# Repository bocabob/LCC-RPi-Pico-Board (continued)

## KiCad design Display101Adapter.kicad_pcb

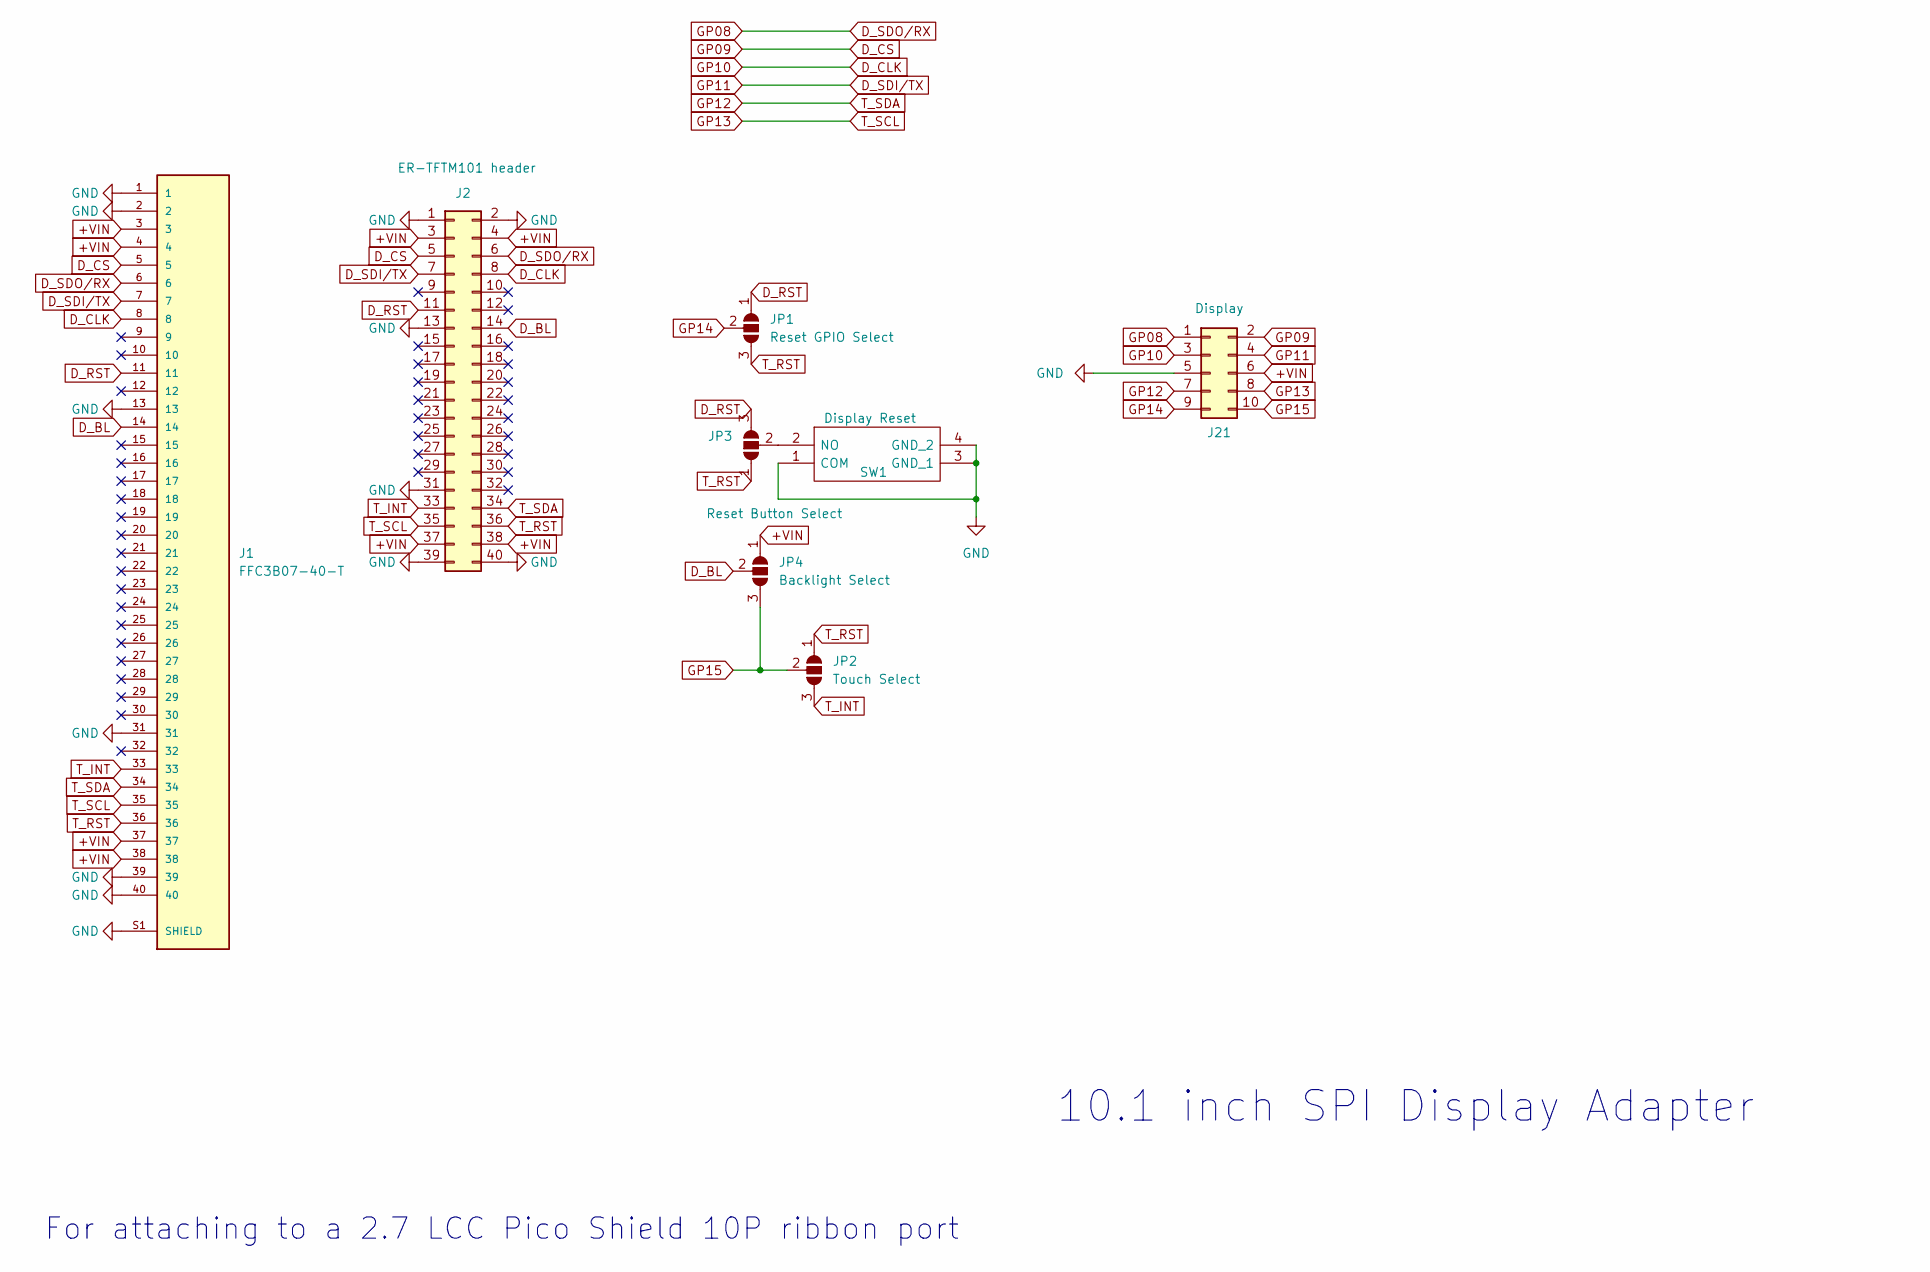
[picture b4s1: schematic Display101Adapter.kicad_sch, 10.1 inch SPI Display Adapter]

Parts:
J1: FFC3B07-40-T; GCT_FFC3B07-40-T; PARTREV A
J2: ER-TFTM101 header; PinSocket_2x20_P2.54mm_Vertical
J21: Display; IDC-Header_2x05_P2.54mm_Vertical
JP1: Reset GPIO Select; SolderJumper-3_P1.3mm_Open_Pad1.0x1.5mm_NumberLabels
JP2: Touch Select; SolderJumper-3_P1.3mm_Open_Pad1.0x1.5mm_NumberLabels
JP3: Reset Button Select; SolderJumper-3_P1.3mm_Open_Pad1.0x1.5mm_NumberLabels
JP4: Backlight Select; SolderJumper-3_P1.3mm_Open_Pad1.0x1.5mm_NumberLabels
SW1: Display Reset; TS1167443BK160RAD; Mouser Part Number 179-TS1167443160RAD

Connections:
+VIN: J1.3, J1.4, J1.37, J1.38, J2.3, J2.4, J2.37, J2.38, J21.6, JP4.1 (A)
D_BL: J1.14, J2.14, JP4.2 (C)
D_CLK: J1.8, J2.8, J21.3
D_CS: J1.5, J2.5, J21.2
D_RST: J1.11, J2.11, JP1.1 (A), JP3.3 (B)
D_SDI/TX: J1.7, J2.7, J21.4
D_SDO/RX: J1.6, J2.6, J21.1
GND: J1.1, J1.2, J1.13, J1.31, J1.39, J1.40, J1.S1 (SHIELD), J1.S2 (SHIELD), J2.1, J2.2, J2.13, J2.31, J2.39, J2.40, J21.5, SW1.1 (COM), SW1.3 (GND_1), SW1.4 (GND_2)
GP12: J1.34, J2.34, J21.7
GP13: J1.35, J2.35, J21.8
GP14: J21.9, JP1.2 (C)
GP15: J21.10, JP2.2 (C), JP4.3 (B)
unnamed: JP3.2 (C), SW1.2 (NO)
T_INT: J1.33, J2.33, JP2.3 (B)
T_RST: J1.36, J2.36, JP1.3 (B), JP2.1 (A), JP3.1 (A)

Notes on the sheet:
10.1 inch SPI Display Adapter
For attaching to a 2.7 LCC Pico Shield 10P ribbon port

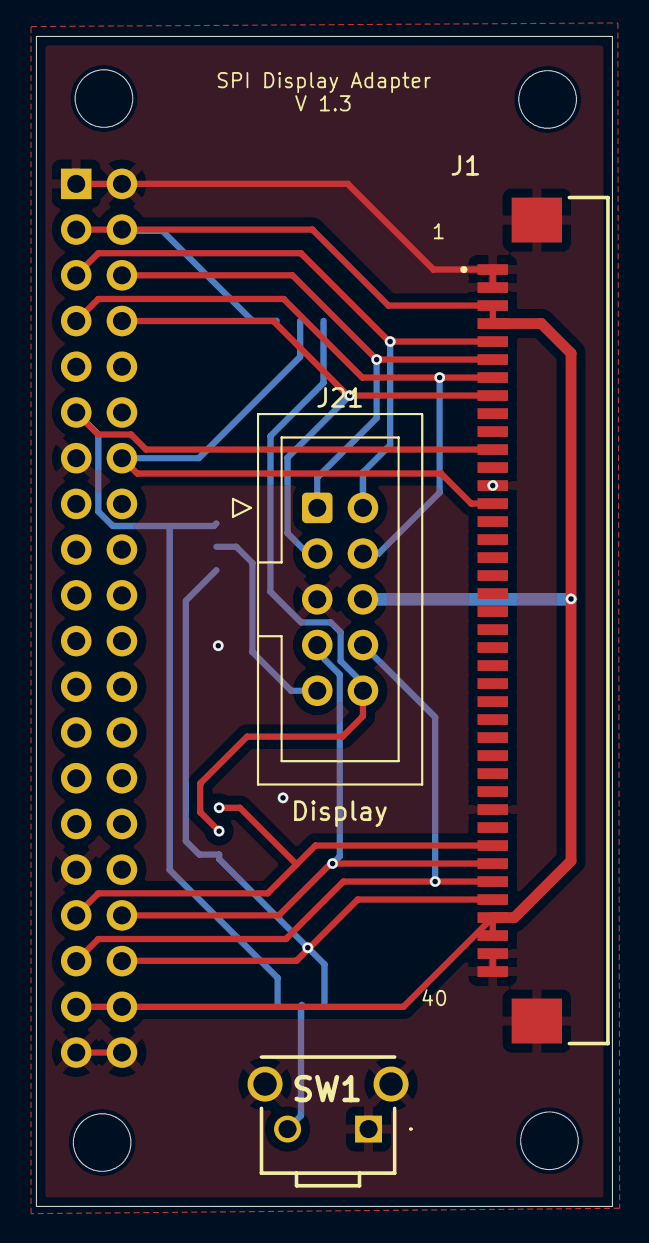
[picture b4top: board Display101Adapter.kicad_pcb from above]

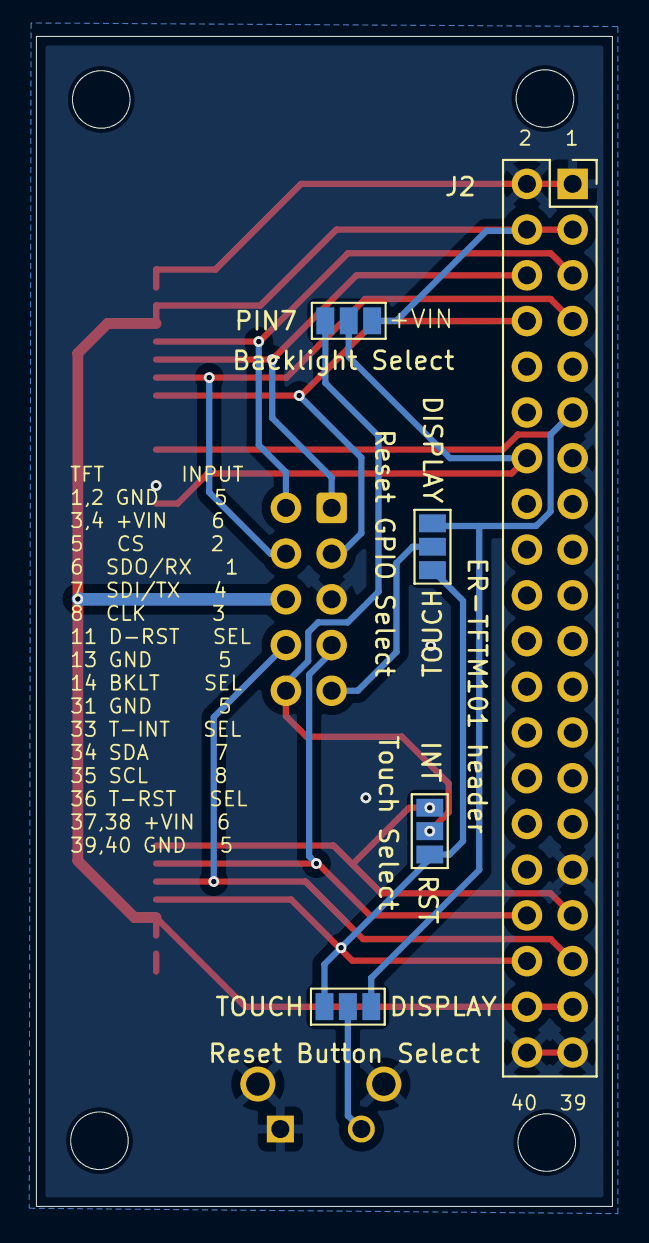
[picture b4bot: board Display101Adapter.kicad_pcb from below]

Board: 2 copper layers, 32.0 x 65.0 mm, 8 parts (5 on the bottom side), 15 nets.

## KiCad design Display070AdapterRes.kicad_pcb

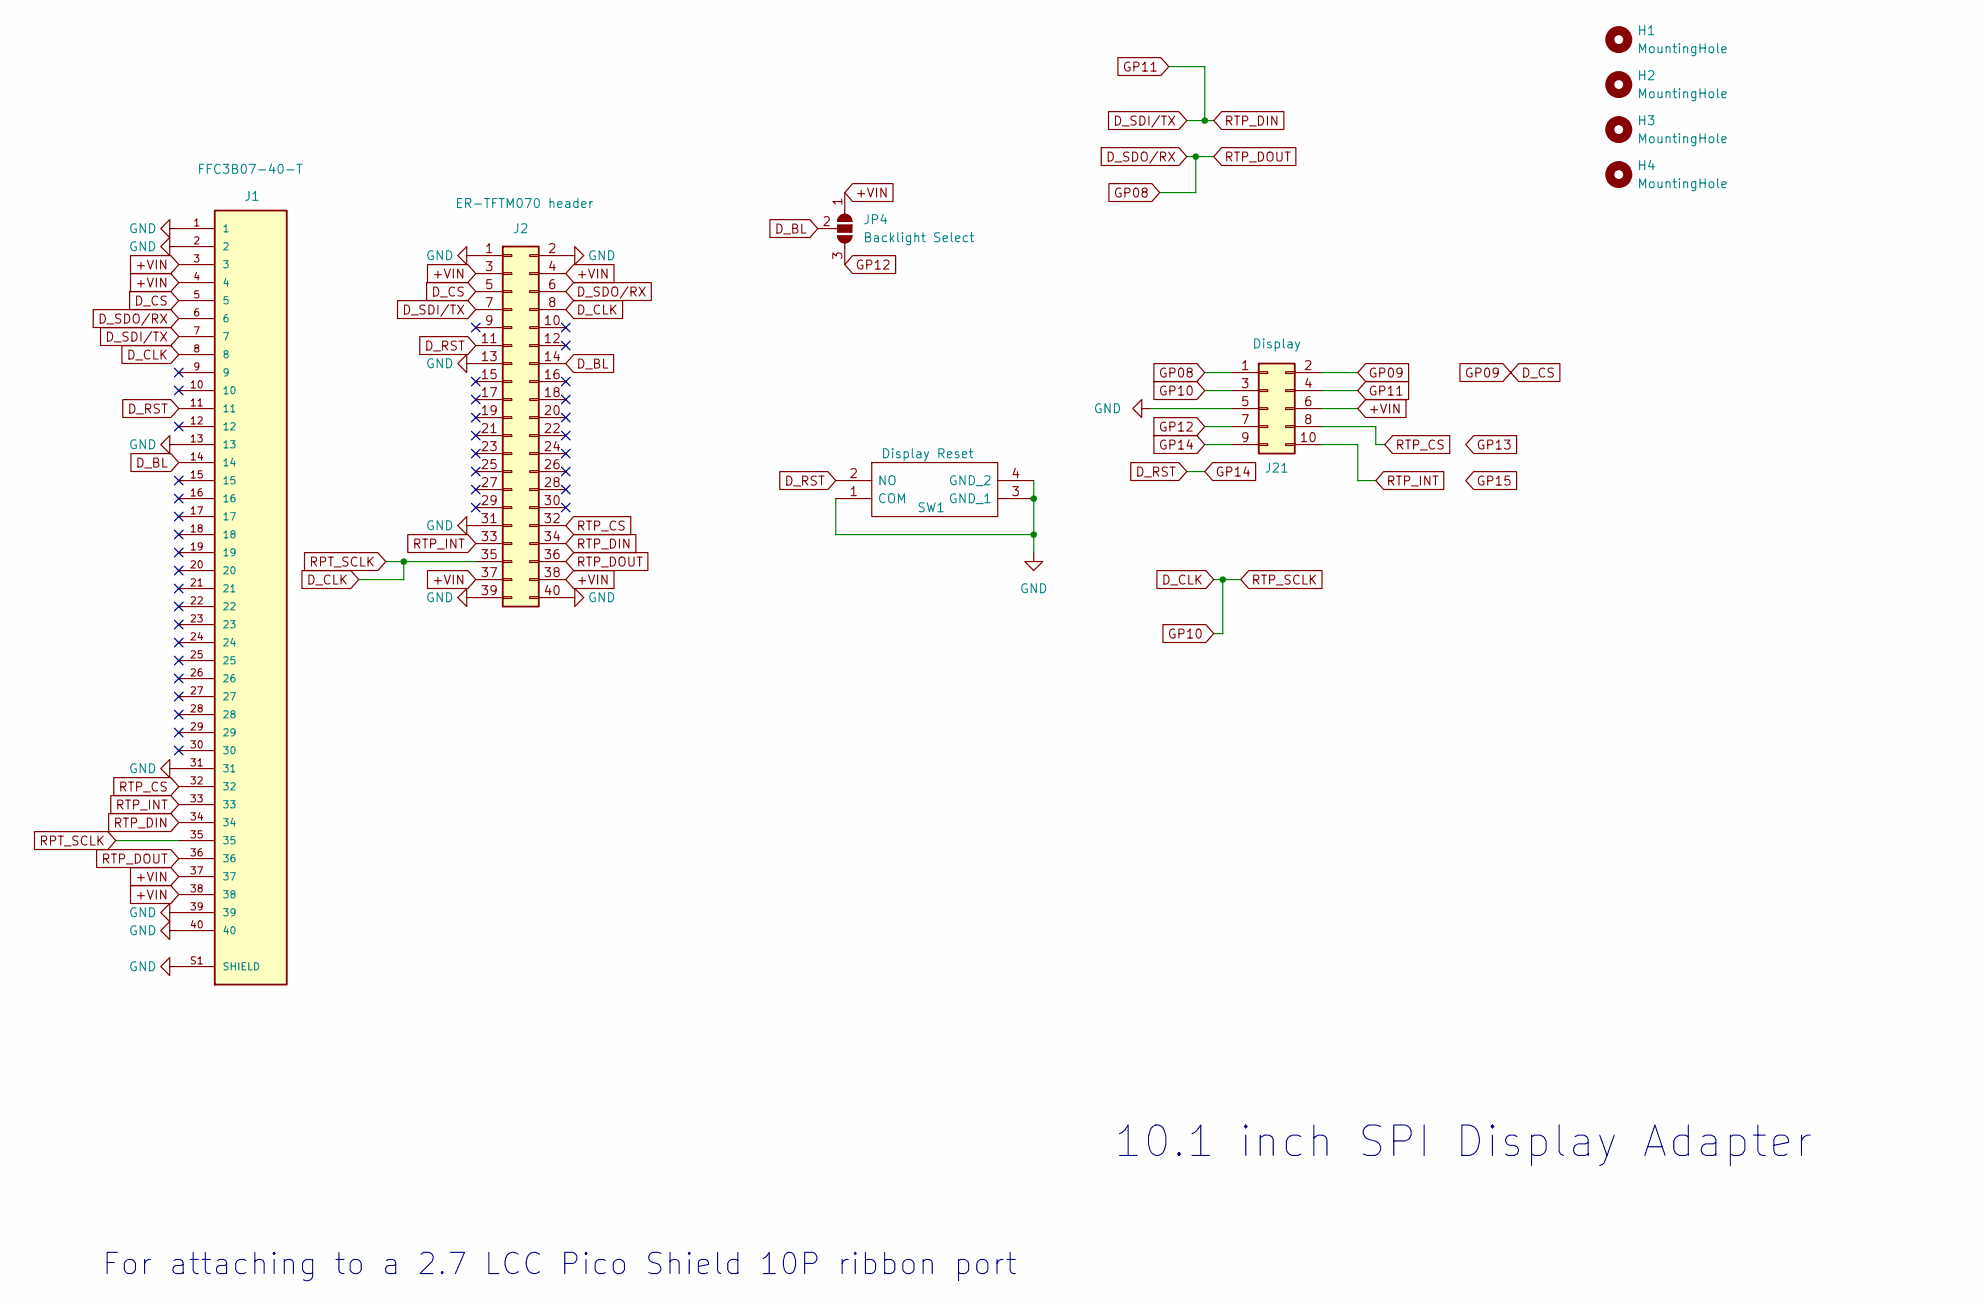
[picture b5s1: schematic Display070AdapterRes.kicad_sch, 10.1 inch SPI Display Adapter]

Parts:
H1, H2, H3, H4: MountingHole; MountingHole_3.5mm
J1: FFC3B07-40-T; GCT_FFC3B07-40-T; PARTREV A
J2: ER-TFTM070 header; PinSocket_2x20_P2.54mm_Vertical
J21: Display; IDC-Header_2x05_P2.54mm_Vertical
JP4: Backlight Select; SolderJumper-3_P1.3mm_Open_Pad1.0x1.5mm_NumberLabels
SW1: Display Reset; TS1167443BK160RAD; Mouser Part Number 179-TS1167443160RAD

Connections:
+VIN: J1.3, J1.4, J1.37, J1.38, J2.3, J2.4, J2.37, J2.38, J21.6, JP4.1 (A)
D_BL: J1.14, J2.14, JP4.2 (C)
D_CLK: J1.8, J1.35, J2.8, J2.35, J21.3
D_CS: J1.5, J2.5, J21.2
D_RST: J1.11, J2.11, J21.9, SW1.2 (NO)
D_SDI/TX: J1.7, J1.34, J2.7, J2.34, J21.4
D_SDO/RX: J1.6, J1.36, J2.6, J2.36, J21.1
GND: J1.1, J1.2, J1.13, J1.31, J1.39, J1.40, J1.S1 (SHIELD), J1.S2 (SHIELD), J2.1, J2.2, J2.13, J2.31, J2.39, J2.40, J21.5, SW1.1 (COM), SW1.3 (GND_1), SW1.4 (GND_2)
GP12: J21.7, JP4.3 (B)
RTP_CS: J1.32, J2.32, J21.8
RTP_INT: J1.33, J2.33, J21.10

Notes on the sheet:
10.1 inch SPI Display Adapter
For attaching to a 2.7 LCC Pico Shield 10P ribbon port

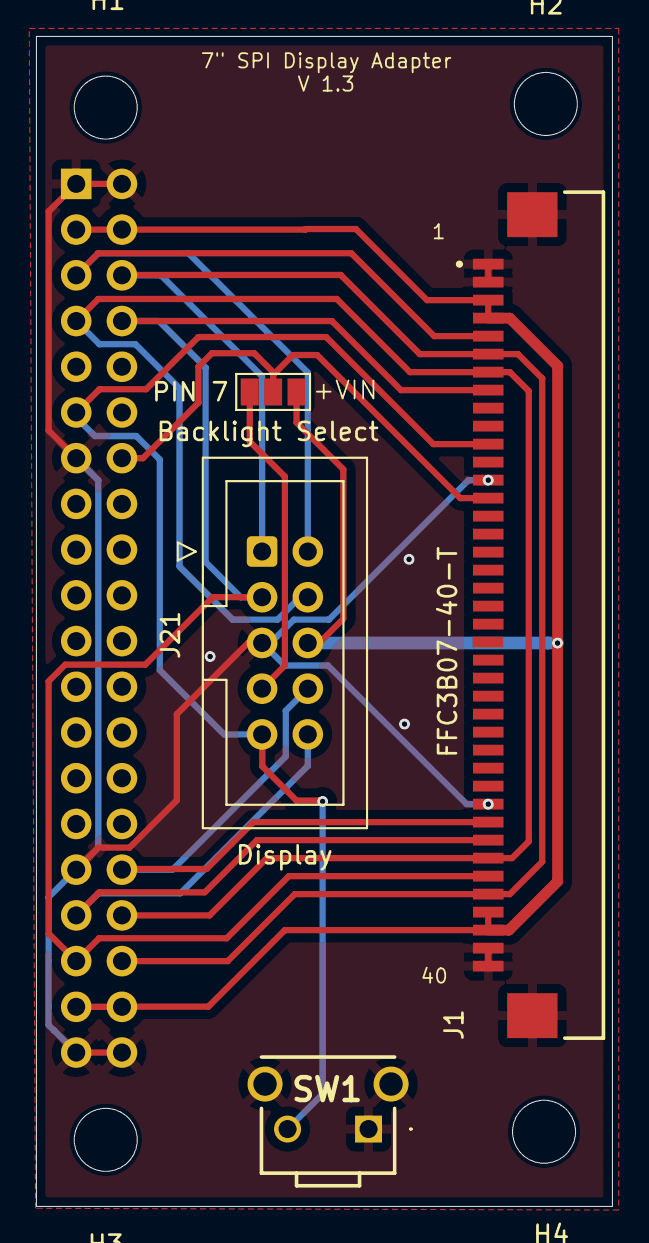
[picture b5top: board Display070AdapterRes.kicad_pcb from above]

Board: 2 copper layers, 32.0 x 65.0 mm, 9 parts (1 on the bottom side), 11 nets.

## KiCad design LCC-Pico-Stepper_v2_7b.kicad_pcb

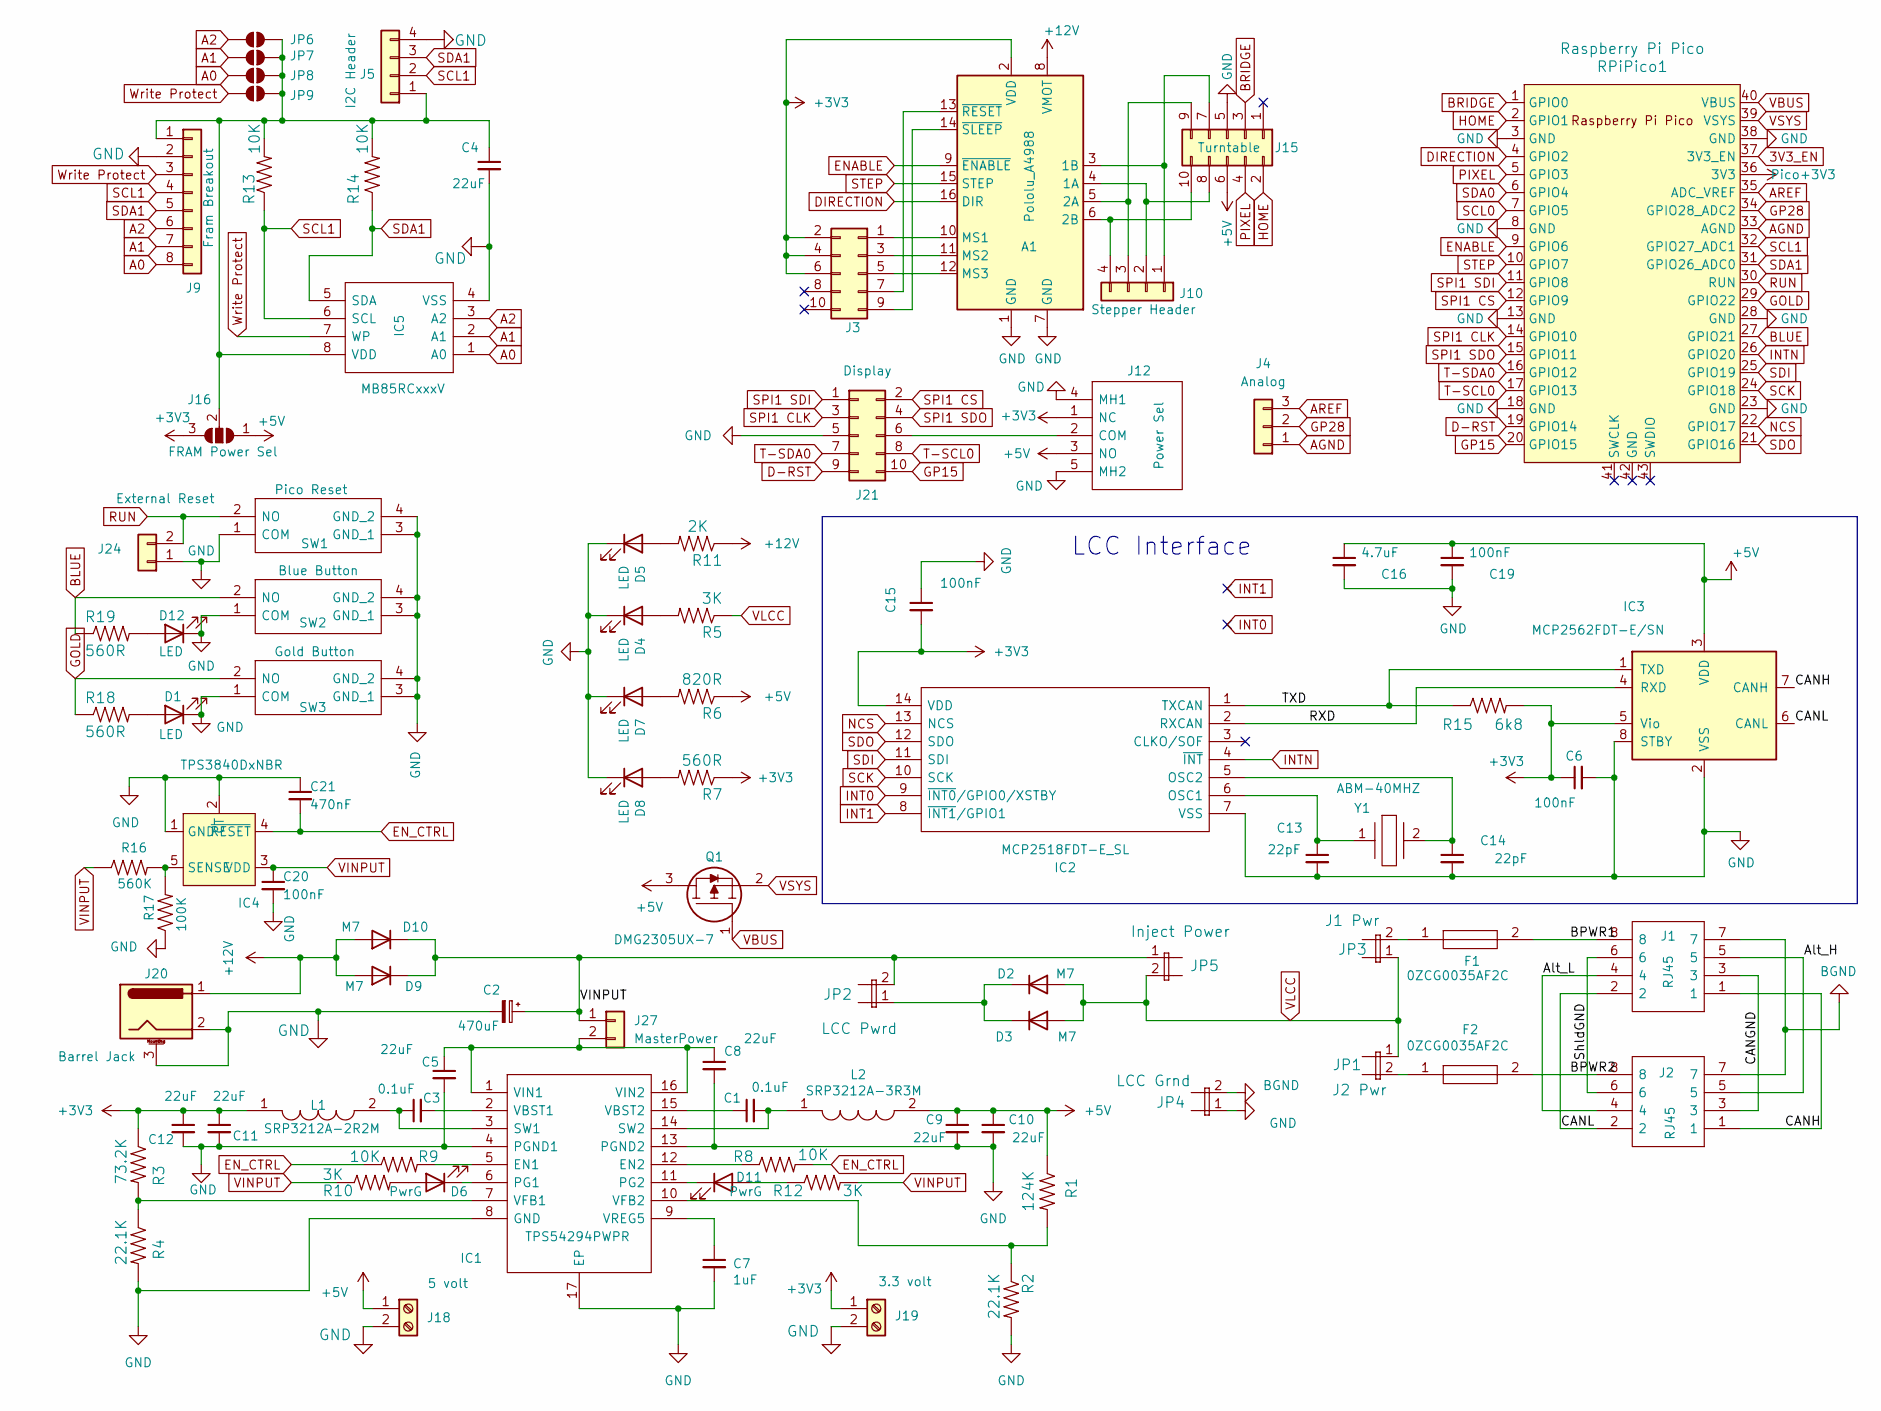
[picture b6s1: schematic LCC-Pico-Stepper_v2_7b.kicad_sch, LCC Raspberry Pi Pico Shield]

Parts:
A1: Pololu_A4988; Pololu_Breakout-16_15.2x20.3mm
C1, C3: 0.1uF; C_1206_3216Metric_Pad1.33x1.80mm_HandSolder
C2: 470uF; CP_Radial_D8.0mm_P3.50mm
C4, C5, C8, C9, C10, C11, C12: 22uF; C_1206_3216Metric_Pad1.33x1.80mm_HandSolder
C6, C15, C19, C20: 100nF; C_1206_3216Metric_Pad1.33x1.80mm_HandSolder
C7: 1uF; C_1206_3216Metric_Pad1.33x1.80mm_HandSolder
C13, C14: 22pF; C_1206_3216Metric_Pad1.33x1.80mm_HandSolder
C16: 4.7uF; C_1206_3216Metric_Pad1.33x1.80mm_HandSolder
C21: 470nF; C_1206_3216Metric_Pad1.33x1.80mm_HandSolder
D1, D4, D5, D7, D8, D12: LED; LED_1206_3216Metric_Pad1.42x1.75mm_HandSolder
D2, D3, D9, D10: M7; DIOM5327X240N
D6, D11: PwrG; LED_1206_3216Metric_Pad1.42x1.75mm_HandSolder
F1, F2: 0ZCG0035AF2C; FUSC4632X70N; Mouser Part Number 530-0ZCG0035AF2C
IC1: TPS54294PWPR; SOP65P640X120-17N; Mouser Part Number 595-TPS54294PWPR
IC2: MCP2518FDT-E_SL; SOIC-14_3.9x8.7mm_P1.27mm; Mouser Part Number 579-MCP2518FDT-E/SL
IC3: MCP2562FDT-E/SN; SOIC-8_3.9x4.9mm_P1.27mm; Mouser Part Number 771-TJA1042T/3/1J
IC4: TPS3840DxNBR; SOT-23-5
IC5: MB85RCxxxV; SOIC127P600X175-8N; Mouser Part Number 249-MB85RC256VPNJNE1
J1, J2: RJ45; MTJ880X1; Mouser Part Number 737-MTJ-880X1
J3: Conn_02x05_Odd_Even; PinHeader_2x05_P2.54mm_Vertical
J4: Analog
J5: I2C Header; PinSocket_1x04_P2.54mm_Vertical
J9: Fram Breakout; PinHeader_1x08_P2.54mm_Vertical
J10: Stepper Header; PinSocket_1x04_P2.54mm_Vertical
J12: Power Sel; SLW8645872ARAND; Mouser Part Number 179-SLW8645872ARAND
J15: Turntable; IDC-Header_2x05_P2.54mm_Vertical
J16: FRAM Power Sel; SolderJumper-3_P1.3mm_Open_RoundedPad1.0x1.5mm
J18: 5 volt; TerminalBlock_TE_282834-2_1x02_P2.54mm_Horizontal
J19: 3.3 volt; TerminalBlock_TE_282834-2_1x02_P2.54mm_Horizontal
J20: Barrel Jack; BarrelJack_Horizontal
J21: Display; IDC-Header_2x05_P2.54mm_Vertical
J24: External Reset; PinHeader_1x02_P2.54mm_Vertical
J27: MasterPower; PinHeader_1x02_P2.54mm_Vertical
JP1: J2 Pwr; PinHeader_1x02_P2.54mm_Vertical
JP2: LCC Pwrd; PinHeader_1x02_P2.54mm_Vertical
JP3: J1 Pwr; PinHeader_1x02_P2.54mm_Vertical
JP4: LCC Grnd; PinHeader_1x02_P2.54mm_Vertical
JP5: Inject Power; PinHeader_1x02_P2.54mm_Vertical
JP6: A2; SolderJumper-2_P1.3mm_Open_Pad1.0x1.5mm
JP7: A1; SolderJumper-2_P1.3mm_Open_Pad1.0x1.5mm
JP8: A0; SolderJumper-2_P1.3mm_Open_Pad1.0x1.5mm
JP9: WP; SolderJumper-2_P1.3mm_Open_Pad1.0x1.5mm
L1: SRP3212A-2R2M; INDC3225X120N; Mouser Part Number 652-SRP3212A-3R3M
L2: SRP3212A-3R3M; INDC3225X120N; Mouser Part Number 652-SRP3212A-3R3M
Q1: DMG2305UX-7; SOT96P240X115-3N; Mouser Part Number 621-DMG2305UX-7
R1: 124K; R_1206_3216Metric_Pad1.30x1.75mm_HandSolder
R2, R4: 22.1K; R_1206_3216Metric_Pad1.30x1.75mm_HandSolder
R3: 73.2K; R_1206_3216Metric_Pad1.30x1.75mm_HandSolder
R5, R10, R12: 3K; R_1206_3216Metric_Pad1.30x1.75mm_HandSolder
R6: 820R; R_1206_3216Metric_Pad1.30x1.75mm_HandSolder
R7, R18, R19: 560R; R_1206_3216Metric_Pad1.30x1.75mm_HandSolder
R8, R9, R13, R14: 10K; R_1206_3216Metric_Pad1.30x1.75mm_HandSolder
R11: 2K; R_1206_3216Metric_Pad1.30x1.75mm_HandSolder
R15: 6k8; R_1206_3216Metric_Pad1.30x1.75mm_HandSolder
R16: 560K; R_1206_3216Metric_Pad1.30x1.75mm_HandSolder
R17: 100K; R_1206_3216Metric_Pad1.30x1.75mm_HandSolder
RPiPico1: Raspberry Pi Pico; RPi_Pico_SMD_TH; PARTREV 12/May/2017
SW1: Pico Reset; TS1167443BK160RAD; Mouser Part Number 179-TS1167443160RAD
SW2: Blue Button; TS1167443BK160RAD; Mouser Part Number 179-TS1167443160RAD
SW3: Gold Button; TS1167443BK160RAD; Mouser Part Number 179-TS1167443160RAD
Y1: ABM-40MHZ; ABM3; Mouser Part Number 815-ABL-40-B2F

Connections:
3V3_EN: RPiPico1.37 (3V3_EN)
+3V3: A1.2 (VDD), C6.1, C11.1, C12.1, C15.2, IC2.14 (VDD), IC3.5 (Vio), J3.2, J3.4, J3.6, J12.1 (NC), J16.3 (B), J19.1, L1.1, R3.1, R7.1, R15.2
+5V: C9.1, C10.1, C16.1, C19.1, IC3.3 (VDD), J12.3 (NO), J15.6, J16.1 (A), J18.1, L2.2, Q1.3, R1.1, R6.1
+12V: A1.8 (VMOT), D9.2 (A), D10.2 (A), J20.1, R11.1
/Alt_H: J1.5, J2.5
/Alt_L: J1.4, J2.4
/BPWR1: F1.2, J1.8
/BPWR2: F2.2, J2.8
/CANGND: J1.3, J2.3
/CANH: IC3.7 (CANH), J1.1, J2.1
/CANL: IC3.6 (CANL), J1.2, J2.2
/RXD: IC2.2 (RXCAN), IC3.4 (RXD)
/ShldGND: J1.6, J2.6
/TXD: IC2.1 (TXCAN), IC3.1 (TXD), R15.1
A0: IC5.1 (A0), J9.8, JP8.1 (A)
A1: IC5.2 (A1), J9.7, JP7.1 (A)
A2: IC5.3 (A2), J9.6, JP6.1 (A)
AGND: J4.1, RPiPico1.33 (AGND)
AREF: J4.3, RPiPico1.35 (ADC_VREF)
BGND: J1.7, J2.7, JP4.2
BLUE: R19.1, RPiPico1.27 (GPIO21), SW2.2 (NO)
BRIDGE: J15.3, RPiPico1.1 (GPIO0)
DIRECTION: A1.16 (DIR), RPiPico1.4 (GPIO2)
ENABLE: A1.9 (~ENABLE), RPiPico1.9 (GPIO6)
EN_CTRL: C21.2, IC4.4 (~RESET), R8.2, R9.1
GND: A1.1 (GND), A1.7 (GND), C2.2, C4.2, C5.2, C6.2, C7.2, C8.2, C9.2, C10.2, C11.2, C12.2, C13.2, C14.2, C15.1, C16.2, C19.2, C20.2, C21.1, D1.1 (K), D4.1 (K), D5.1 (K), D7.1 (K), D8.1 (K), D12.1 (K), IC1.4 (PGND1), IC1.8 (GND), IC1.13 (PGND2), IC1.17 (EP), IC2.7 (VSS), IC3.2 (VSS), IC3.8 (STBY), IC4.1 (GND), IC4.2 (CT), IC5.4 (VSS), J5.4, J9.2, J12.4 (MH1), J12.5 (MH2), J15.5, J18.2, J19.2, J20.2, J20.3, J21.5, J24.1, JP4.1, R2.2, R4.2, R17.1, RPiPico1.3 (GND), RPiPico1.8 (GND), RPiPico1.13 (GND), RPiPico1.18 (GND), RPiPico1.23 (GND), RPiPico1.28 (GND), RPiPico1.38 (GND), SW1.1 (COM), SW1.3 (GND_1), SW1.4 (GND_2), SW2.1 (COM), SW2.3 (GND_1), SW2.4 (GND_2), SW3.1 (COM), SW3.3 (GND_1), SW3.4 (GND_2)
GOLD: R18.1, RPiPico1.29 (GPIO22), SW3.2 (NO)
GP12: J21.7, RPiPico1.16 (GPIO12)
GP28: J4.2, RPiPico1.34 (GPIO28_ADC2)
HOME: J15.2, RPiPico1.2 (GPIO1)
INT0: IC2.9 (~INT0/GPIO0/XSTBY)
INT1: IC2.8 (~INT1/GPIO1)
INTN: IC2.4 (~INT), RPiPico1.26 (GPIO20)
NCS: IC2.13 (NCS), RPiPico1.22 (GPIO17)
unnamed: A1.4 (1A), J10.2, J15.8
unnamed: A1.3 (1B), J10.1, J15.7
unnamed: A1.5 (2A), J10.3, J15.9
unnamed: A1.6 (2B), J10.4, J15.10
unnamed: A1.10 (MS1), J3.1
unnamed: A1.11 (MS2), J3.3
unnamed: A1.12 (MS3), J3.5
unnamed: A1.13 (~RESET), J3.7
unnamed: A1.14 (~SLEEP), J3.9
unnamed: D1.2 (A), R18.2
unnamed: D2.1 (K), D3.1 (K), JP2.1
unnamed: D4.2 (A), R5.2
unnamed: D5.2 (A), R11.2
unnamed: D6.2 (A), R10.2
unnamed: D6.1 (K), IC1.6 (PG1)
unnamed: D7.2 (A), R6.2
unnamed: D8.2 (A), R7.2
unnamed: D11.2 (A), R12.1
unnamed: D11.1 (K), IC1.11 (PG2)
unnamed: D12.2 (A), R19.2
unnamed: F1.1, JP3.2
unnamed: F2.1, JP1.2
unnamed: IC1.5 (EN1), R9.2
unnamed: IC1.12 (EN2), R8.1
unnamed: C3.1, IC1.3 (SW1), L1.2
unnamed: C1.2, IC1.14 (SW2), L2.1
unnamed: C3.2, IC1.2 (VBST1)
unnamed: C1.1, IC1.15 (VBST2)
unnamed: IC1.7 (VFB1), R3.2, R4.1
unnamed: IC1.10 (VFB2), R1.2, R2.1
unnamed: C5.1, C8.1, IC1.1 (VIN1), IC1.16 (VIN2), J27.2
unnamed: C7.1, IC1.9 (VREG5)
unnamed: C13.1, IC2.6 (OSC1), Y1.1
unnamed: C14.1, IC2.5 (OSC2), Y1.2
unnamed: IC4.5 (SENSE), R16.2, R17.2
unnamed: C4.1, IC5.8 (VDD), J5.1, J9.1, J16.2 (C), JP6.2 (B), JP7.2 (B), JP8.2 (B), JP9.2 (B), R13.2, R14.2
unnamed: J12.2 (COM), J21.6
PIXEL: J15.4, RPiPico1.5 (GPIO3)
Pico+3V3: RPiPico1.36 (3V3)
RUN: J24.2, RPiPico1.30 (RUN), SW1.2 (NO)
SCK: IC2.10 (SCK), RPiPico1.24 (GPIO18)
SCL0: RPiPico1.7 (GPIO5)
SCL1: IC5.6 (SCL), J5.2, J9.4, R13.1, RPiPico1.32 (GPIO27_ADC1)
SDA1: IC5.5 (SDA), J5.3, J9.5, R14.1, RPiPico1.31 (GPIO26_ADC0)
SDI: IC2.11 (SDI), RPiPico1.25 (GPIO19)
SDO: IC2.12 (SDO), RPiPico1.21 (GPIO16)
SPI1 CLK: J21.3, RPiPico1.14 (GPIO10)
SPI1 CS: J21.2, RPiPico1.12 (GPIO9)
SPI1 SDI: J21.1, RPiPico1.11 (GPIO8)
SPI1 SDO: J21.4, RPiPico1.15 (GPIO11)
STEP: A1.15 (STEP), RPiPico1.10 (GPIO7)
T-INT: J21.8, RPiPico1.17 (GPIO13)
T-SCL0: J21.10, RPiPico1.20 (GPIO15)
VBUS: Q1.1, RPiPico1.40 (VBUS)
VINPUT: C2.1, C20.1, D9.1 (K), D10.1 (K), IC4.3 (VDD), J27.1, JP2.2, JP5.1, R10.1, R12.2, R16.1
VLCC: D2.2 (A), D3.2 (A), JP1.1, JP3.1, JP5.2, R5.1
VSYS: Q1.2, RPiPico1.39 (VSYS)
Write Protect: IC5.7 (WP), J9.3, JP9.1 (A)

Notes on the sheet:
LCC Interface

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
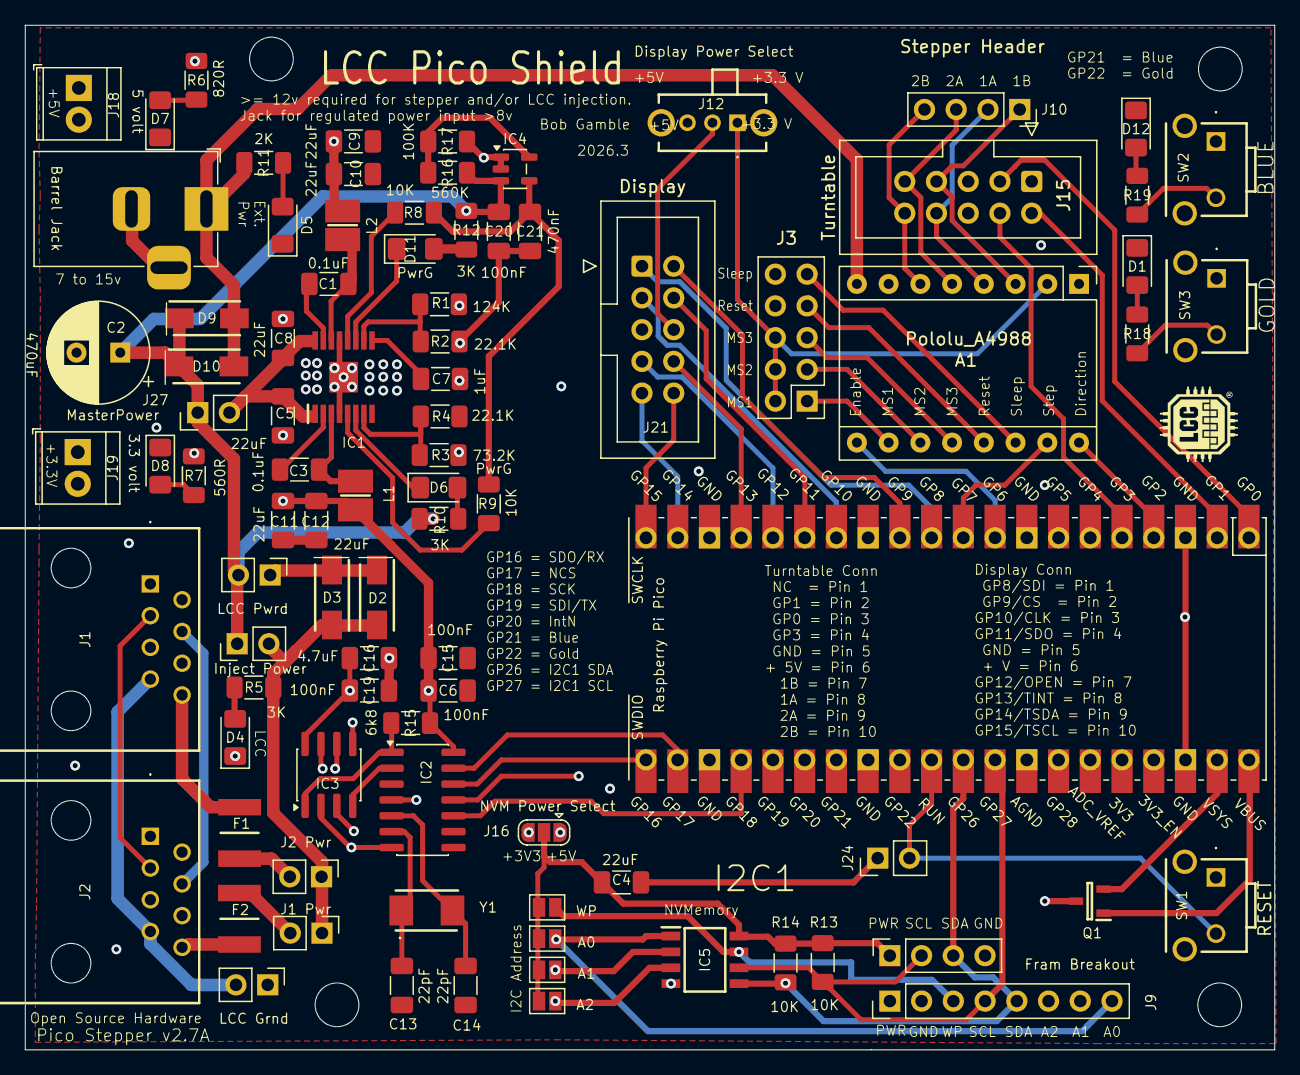
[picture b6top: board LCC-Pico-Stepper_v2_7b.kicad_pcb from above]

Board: 4 copper layers, 100.0 x 82.0 mm, 90 parts (0 on the bottom side), 85 nets.

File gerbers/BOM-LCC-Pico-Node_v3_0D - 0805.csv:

Comment,Designator,Footprint,LCSC,Quantity
0ZCG0050AF2C,"F1,F2",FUSC4632X70N,C3762102,2
100nF,"C1,C15,C19,C3,C6",C_0805_2012Metric,C49678,5
10K,"R13,R14,R8,R9",R_0805_2012Metric,C17414,4
10nF,"C17,C22",C_0805_2012Metric,C1710,2
124K,R1,R_0805_2012Metric,C2902861,1
1uF,"C18,C7",C_0805_2012Metric,C28323,2
22.1K,"R2,R4",R_0805_2012Metric,C865310,2
22pF,"C13,C14",C_0805_2012Metric,C1804,2
22uF,"C10,C11,C12,C4,C5,C8,C9",C_0805_2012Metric,C45783,7
256Kb,IC5,SOIC127P600X175-8N,C90485,1
2K,R11,R_0805_2012Metric,C17604,1
3.3uH,L1,L_1210_3225Metric,C337905,1
3K,R5,R_0805_2012Metric,C17661,1
4.7uF,C16,C_0805_2012Metric,C1779,1
4.7uH,L2,L_1210_3225Metric,C1330201,1
470uF,C2,CP_Elec_8x10.5,C48935389,1
560R,"R18,R19,R7",R_0805_2012Metric,C28636,3
6k8,R15,R_0805_2012Metric,C17772,1
73.2K,R3,R_0805_2012Metric,C422816,1
820R,R6,R_0805_2012Metric,C17837,1
ABM-40MHZ,Y1,ABM3,C1986264,1
Barrel Jack,J20,DC-050_SMD,C431534,1
DMG2305UX-7,Q1,SOT96P240X115-3N,C150470,1
LED,"D1,D12,D4,D5,D7,D8",LED_0805_2012Metric,C2297,6
M7,"D10,D2,D3,D9",D_SMA,C22448047,4
MCP2518FD,IC2,SOIC-14_3.9x8.7mm_P1.27mm,C626758,1
MCP2562FD,IC3,SOIC-8_3.9x4.9mm_P1.27mm,C511335,1
RJ45,"J1,J2",MTJ880X1,C7235899,2
TPS54228DR,"IC1,IC6",SOIC127P600X170-9N,C263275,2
button,"SW1,SW2,SW3",SW_Push_1P1T_XKB_TS-1187A,C318884,3
I/O - 1,J21,IDC-Header_2x05_P2.54mm_Vertical,,1
Raspberry Pi Pico,RPiPico1,RPi_Pico_SMD_TH,,1
Ext. Reset,J24,PinHeader_1x02_P2.54mm_Vertical,,1
Power Sel,J6,SLW8645872ARAND,,1
External Power,J5,"PhoenixContact_MSTBA_2,5_2-G-5,08_1x02_P5.08mm_Horizontal",,1
Analog I/O,J15,IDC-Header_2x03_P2.54mm_Vertical,,1
LCC Pwr Sel,J3,SLW8645872ARAND,,1
Power Sel,J12,SLW8645872ARAND,,1
I/O - 2,J4,IDC-Header_2x05_P2.54mm_Vertical,,1
MasterPower,J27,PinHeader_1x02_P2.54mm_Vertical,,1
External Power,J7,JST_EH_B3B-EH-A_1x03_P2.50mm_Vertical,,1

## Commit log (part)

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2026-01-22 Initial Load
    put the files in the right place
2026-01-23 Added Documentation
    Added some board documentation
2026-04-27 2026 Spring Board Updates
    updates for stepper board for SPI display and node boards and breakout boards for IDC cables
2026-04-28 Documentation Updates
    added a bunch
2026-04-29 Guide updates
2026-06-20 Delete old boards
    Delete old flawed boards, v 3.0 boards are much better.
2026-06-20 v3.0 added
2026-06-23 Production level
    0805 boards can be assembled at JLCPCB with these files
    1206 boards are for hand assembly
2026-06-24 Fixed a problem file
    a footprint got rotated by accident
2026-06-24 User Guide update
